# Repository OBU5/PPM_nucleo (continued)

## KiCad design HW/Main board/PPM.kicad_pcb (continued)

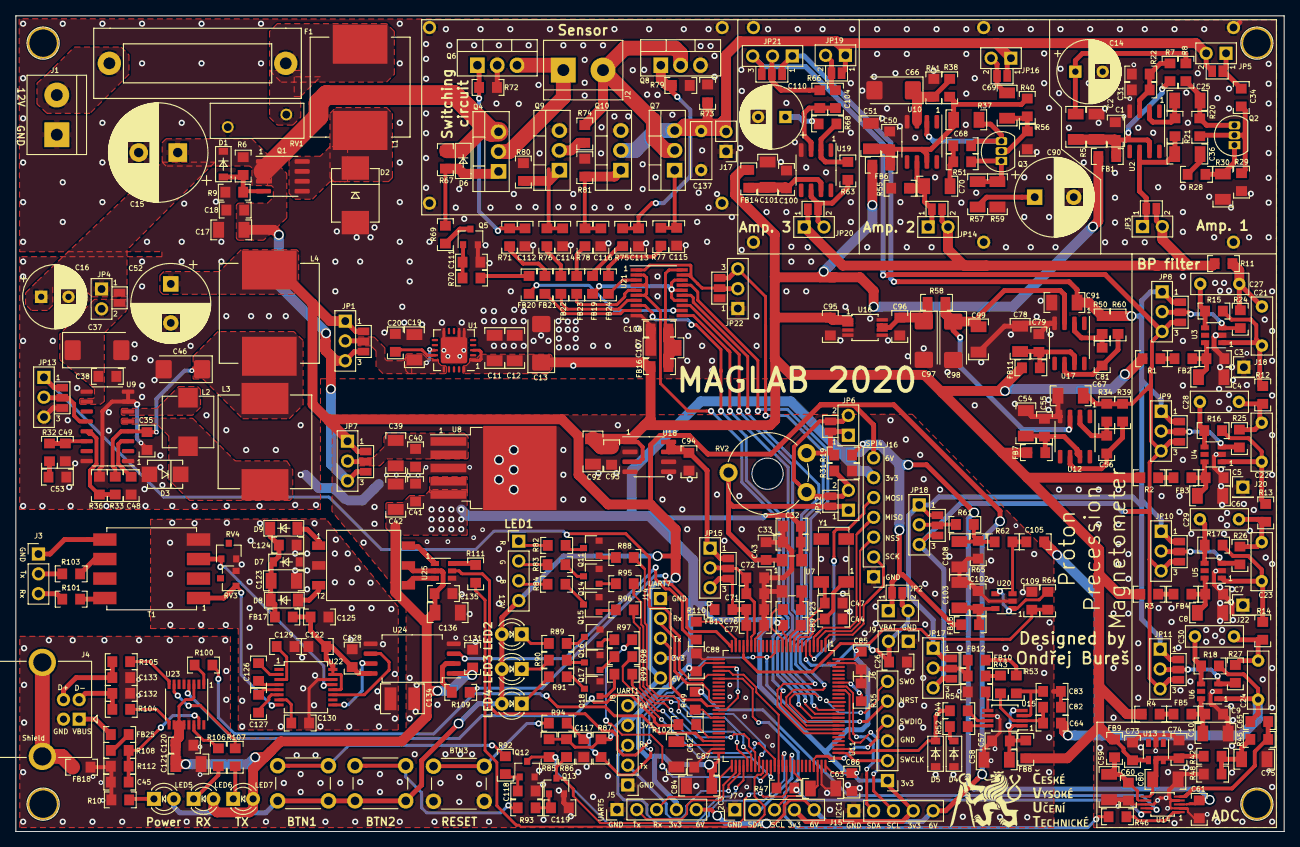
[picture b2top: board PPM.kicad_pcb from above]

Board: 2 copper layers, 162.5 x 104.5 mm, 400 parts (0 on the bottom side), 253 nets.

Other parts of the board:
C70: 22u; C1206
C81: 1u; C0805
C91: 10u; C1206
C111: 10n; C0805
C112, C113, C114, C115, C116: 100n; C0805
C137: C_res; C_Rect_L7.2mm_W2.5mm_P5.00mm_FKS2_FKP2_MKS2_MKP2
D6: 15V; D_SOD-123
J2: PPM_sensor; TerminalBlock_2pin_Pitch5.08mm
J17: C ext; PinHeader_1x02_P2.54mm_Vertical
Q4: IRF9640; TO-220-3_Vertical
Q5: BC847; SOT-23
Q6, Q7, Q9, Q10: IRF740; TO-220-3_Vertical
Q8: IRF640; TO-220-3_Vertical
R50, R67: 2k2; R0805
R55: 47k; R0805
R60: 47; R0805
R69: 1k; R0805
R70: 4k7; R0805
R71, R75, R76, R77, R78: 470; R0805
R72, R73, R79, R80, R81: 100k; R0805
R74: 10k; R0805

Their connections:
+12V: D6.1, Q4.3, R67.1; also elsewhere on the board
GNDA: C91.2, C111.2, C112.2, C113.2, C114.2, C115.2, C116.2, C137.2, J17.1, Q5.2, Q6.2, Q8.3, Q9.3, Q10.3, R55.2, R72.2, R73.2, R79.2, R80.2, R81.2; also elsewhere on the board
unnamed: C111.1, Q5.1, R70.2
unnamed: C112.1, Q6.1, R71.2, R72.1
unnamed: C113.1, Q8.1, R75.2, R79.1
unnamed: C114.1, Q9.1, R76.2, R80.1
unnamed: C115.1, Q7.1, R77.2
unnamed: C116.1, Q10.1, R78.2, R81.1
unnamed: D6.2, Q4.1, R67.2, R69.1
unnamed: J2.1, Q4.2, Q6.3
unnamed: J2.2, Q7.2, Q8.2, R74.1
unnamed: Q5.3, R69.2
unnamed: Q9.2, R74.2
S1_FET: R75.1; also elsewhere on the board
S2_FET: R77.1; also elsewhere on the board
S3_FET: R78.1; also elsewhere on the board
S4_FET: R70.1; also elsewhere on the board
S5_FET: R71.1; also elsewhere on the board
S6_FET: R76.1; also elsewhere on the board
Sig: C137.1, J17.2, Q7.3, Q10.2, R73.1; also elsewhere on the board

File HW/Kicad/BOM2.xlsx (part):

Ref | Value | Part | Footprint | Description | Code | count | which shopping cart | Column3 | Column6 | Column7 | Column8 | Column9 | Column10 | Column11 | Column12 | Column13 | Column14 | Column15 | Column16 | Column17 | Column18 | Column19 | Column20 | Column21 | Column22 | Column23 | Column24 | Column25 | Column26 | Column27 | Column28 | Column29 | Column30 | Column31 | Column32 | Column33 | Column34 | Column35 | Column36 | Column37 | Column38 | Column39 | Column40 | Column41 | Column42 | Column43 | Column44 | Column45 | Column46 | Column47 | Column48 | Column49 | Column50 | Column51 | Column52 | Column53 | Column54 | Column55 | Column56 | Column57 | Column58 | Column59 | Column60 | Column61 | Column62 | Column63 | Column64 | Column65 | Column66 | Column67 | Column68 | Column69 | Column70 | Column71 | Column72 | Column73 | Column74 | Column75 | Column76 | Column77 | Column78 | Column79 | Column80 | Column81 | Column82 | Column83 | Column84 | Column85 | Column86 | Column87 | Column88 | Column89 | Column90 | Column91 | Column92 | Column93 | Column94 | Column95 | Column96 | Column97 | Column98 | Column99 | Column100 | Column101 | Column102 | Column103 | Column104 | Column105 | Column106 | Column107 | Column108 | Column109 | Column110 | Column111 | Column112 | Column113 | Column114 | Column115 | Column116 | Column117 | Column118 | Column119 | Column120 | Column121 | Column122 | Column123 | Column124 | Column125 | Column126 | Column127 | Column128 | Column129 | Column130 | Column131 | Column132 | Column133 | Column134 | Column135 | Column136 | Column137 | Column138 | Column139 | Column140 | Column141 | Column142 | Column143 | Column144 | Column145 | Column146 | Column147 | Column148 | Column149 | Column150 | Column151 | Column152 | Column153 | Column154 | Column155 | Column156 | Column157 | Column158 | Column159 | Column160 | Column161 | Column162 | Column163 | Column164 | Column165 | Column166 | Column167 | Column168 | Column169 | Column170 | Column171 | Column172 | Column173 | Column174 | Column175 | Column176 | Column177 | Column178 | Column179 | Column180 | Column181 | Column182 | Column183 | Column184 | Column185 | Column186 | Column187 | Column188 | Column189 | Column190 | Column191 | Column192 | Column193 | Column194 | Column195 | Column196 | Column197 | Column198 | Column199 | Column200 | Column201 | Column202 | Column203 | Column204 | Column205 | Column206 | Column207 | Column208 | Column209 | Column210 | Column211 | Column212 | Column213 | Column214 | Column215 | Column216 | Column217 | Column218 | Column219 | Column220 | Column221 | Column222 | Column223 | Column224 | Column225 | Column226 | Column227 | Column228 | Column229 | Column230 | Column231 | Column232 | Column233 | Column234 | Column235 | Column236 | Column237 | Column238 | Column239 | Column240 | Column241 | Column242 | Column243 | Column244 | Column245 | Column246 | Column247 | Column248 | Column249 | Column250 | Column251 | Column252 | Column253 | Column254 | Column255 | Column256 | Column257 | Column258 | Column259 | Column260 | Column261 | Column262 | Column263 | Column264 | Column265 | Column266 | Column267 | Column268 | Column269 | Column270 | Column271 | Column272 | Column273 | Column274 | Column275 | Column276 | Column277 | Column278 | Column279 | Column280 | Column281 | Column282 | Column283 | Column284 | Column285 | Column286 | Column287 | Column288 | Column289 | Column290 | Column291 | Column292 | Column293 | Column294 | Column295 | Column296 | Column297 | Column298 | Column299 | Column300 | Column301 | Column302 | Column303 | Column304 | Column305 | Column306 | Column307 | Column308 | Column309 | Column310 | Column311 | Column312 | Column313 | Column314 | Column315 | Column316 | Column317 | Column318 | Column319 | Column320 | Column321 | Column322 | Column323 | Column324 | Column325 | Column326 | Column327 | Column328 | Column329 | Column330 | Column331 | Column332 | Column333 | Column334 | Column335 | Column336 | Column337 | Column338 | Column339 | Column340 | Column341 | Column342 | Column343 | Column344 | Column345 | Column346 | Column347 | Column348 | Column349 | Column350 | Column351 | Column352 | Column353 | Column354 | Column355 | Column356 | Column357 | Column358 | Column359 | Column360 | Column361 | Column362 | Column363 | Column364 | Column365 | Column366 | Column367 | Column368 | Column369 | Column370 | Column371 | Column372 | Column373 | Column374 | Column375 | Column376 | Column377 | Column378 | Column379 | Column380 | Column381 | Column382 | Column383 | Column384 | Column385 | Column386 | Column387 | Column388 | Column389 | Column390 | Column391 | Column392 | Column393 | Column394 | Column395 | Column396 | Column397 | Column398 | Column399 | Column400 | Column401 | Column402 | Column403 | Column404 | Column405 | Column406 | Column407 | Column408 | Column409 | Column410 | Column411 | Column412 | Column413 | Column414 | Column415 | Column416 | Column417 | Column418 | Column419 | Column420 | Column421 | Column422 | Column423 | Column424 | Column425 | Column426 | Column427 | Column428 | Column429 | Column430 | Column431 | Column432 | Column433 | Column434 | Column435 | Column436 | Column437 | Column438 | Column439 | Column440 | Column441 | Column442 | Column443 | Column444 | Column445 | Column446 | Column447 | Column448 | Column449 | Column450 | Column451 | Column452 | Column453 | Column454 | Column455 | Column456 | Column457 | Column458 | Column459 | Column460 | Column461 | Column462 | Column463 | Column464 | Column465 | Column466 | Column467 | Column468 | Column469 | Column470 | Column471 | Column472 | Column473 | Column474 | Column475 | Column476 | Column477 | Column478 | Column479 | Column480 | Column481 | Column482 | Column483 | Column484 | Column485 | Column486 | Column487 | Column488 | Column489 | Column490 | Column491 | Column492 | Column493 | Column494 | Column495 | Column496 | Column497 | Column498 | Column499 | Column500 | Column501 | Column502 | Column503 | Column504 | Column505 | Column506 | Column507 | Column508 | Column509 | Column510 | Column511 | Column512 | Column513 | Column514 | Column515 | Column516 | Column517 | Column518 | Column519 | Column520 | Column521 | Column522 | Column523 | Column524 | Column525 | Column526 | Column527 | Column528 | Column529 | Column530 | Column531 | Column532 | Column533 | Column534 | Column535 | Column536 | Column537 | Column538 | Column539 | Column540 | Column541 | Column542 | Column543 | Column544 | Column545 | Column546 | Column547 | Column548 | Column549 | Column550 | Column551 | Column552 | Column553 | Column554 | Column555 | Column556 | Column557 | Column558 | Column559 | Column560 | Column561 | Column562 | Column563 | Column564 | Column565 | Column566 | Column567 | Column568 | Column569 | Column570 | Column571 | Column572 | Column573 | Column574 | Column575 | Column576 | Column577 | Column578 | Column579 | Column580 | Column581 | Column582 | Column583 | Column584 | Column585 | Column586 | Column587 | Column588 | Column589 | Column590 | Column591 | Column592 | Column593 | Column594 | Column595 | Column596 | Column597 | Column598 | Column599 | Column600 | Column601 | Column602 | Column603 | Column604 | Column605 | Column606 | Column607 | Column608 | Column609 | Column610 | Column611 | Column612 | Column613 | Column614 | Column615 | Column616 | Column617 | Column618 | Column619 | Column620 | Column621 | Column622 | Column623 | Column624 | Column625 | Column626 | Column627 | Column628 | Column629 | Column630 | Column631 | Column632 | Column633 | Column634 | Column635 | Column636 | Column637 | Column638 | Column639 | Column640 | Column641 | Column642 | Column643 | Column644 | Column645 | Column646 | Column647 | Column648 | Column649 | Column650 | Column651 | Column652 | Column653 | Column654 | Column655 | Column656 | Column657 | Column658 | Column659 | Column660 | Column661 | Column662 | Column663 | Column664 | Column665 | Column666 | Column667 | Column668 | Column669 | Column670 | Column671 | Column672 | 
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
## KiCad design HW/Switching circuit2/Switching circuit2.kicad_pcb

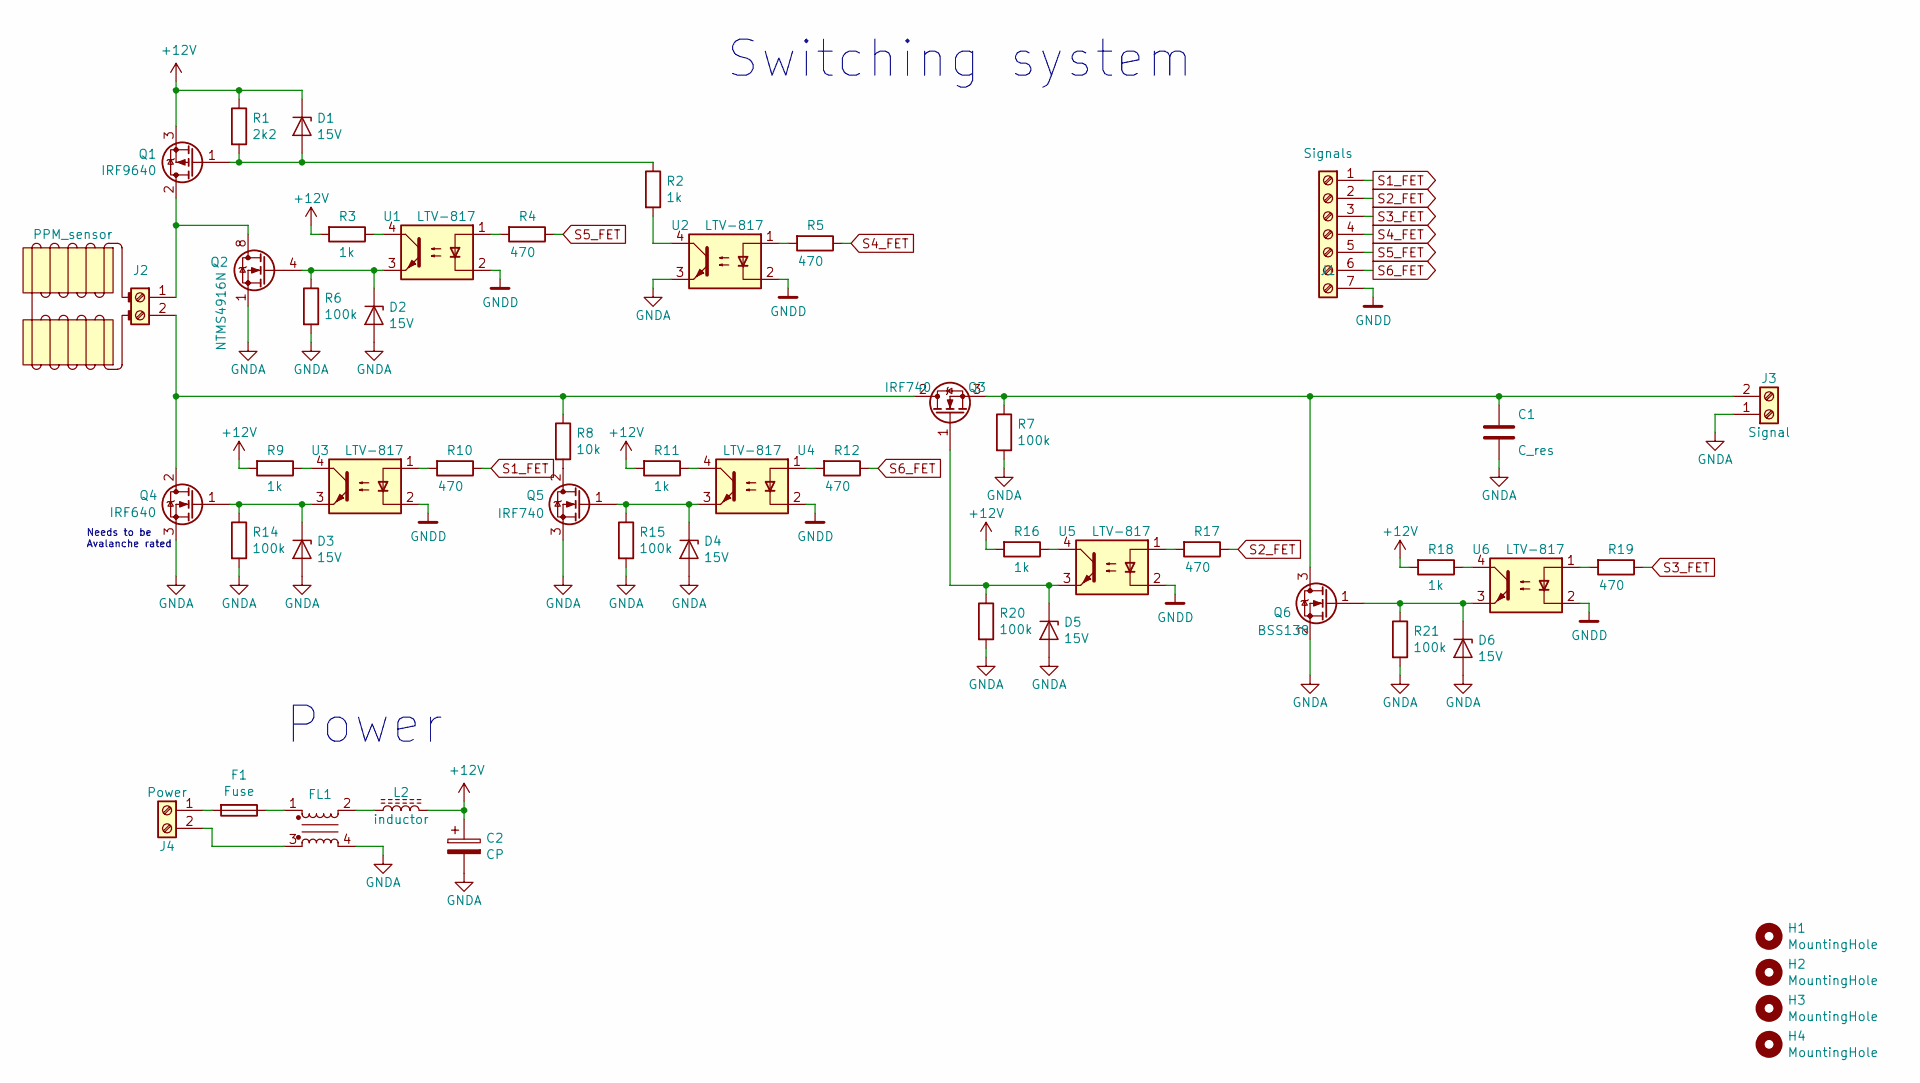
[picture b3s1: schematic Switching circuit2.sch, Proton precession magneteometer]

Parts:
C1: C_res; PinHeader_1x02_P2.54mm_Vertical
C2: CP; CP_Radial_D12.5mm_P5.00mm
D1, D2, D3, D4, D5, D6: 15V; D_SOD-123
F1: Fuse; Fuse_Holder-PTF15
FL1: EMI_Filter_CommonMode; Choke1
H1, H2, H3, H4: MountingHole; Screwh_hole-3.5mm
J1: Signals; PinHeader_1x07_P2.54mm_Vertical
J2: PPM_sensor; TerminalBlock_2pin_Pitch5.08mm
J3: Signal; PinHeader_1x02_P2.54mm_Vertical
J4: Power; TerminalBlock_2pin_Pitch5.08mm
L2: inductor; Inductor_SRR1208
Q1: IRF9640; TO-220-3_Vertical
Q2: NTMS4916N; SOIC-8_3.9x4.9mm_P1.27mm
Q3, Q5: IRF740; TO-220-3_Vertical
Q4: IRF640; TO-220-3_Vertical
Q6: BSS138; SOT-23
R1: 2k2; R1206
R2, R3, R9, R11, R16, R18: 1k; R1206
R4, R5, R10, R12, R17, R19: 470; R1206
R6, R7, R14, R15, R20, R21: 100k; R1206
R8: 10k; R1206
U1, U2, U3, U4, U5, U6: LTV-817; DIP-4_W8.89mm_SMDSocket_LongPads

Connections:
+12V: C2.1, D1.1 (K), L2.2, Q1.3 (S), R1.1, R3.2, R9.2, R11.2, R16.2, R18.2
GNDA: C1.2, C2.2, D2.2 (A), D3.2 (A), D4.2 (A), D5.2 (A), D6.2 (A), FL1.4, J3.1, Q2.1 (S), Q2.2 (S), Q2.3 (S), Q4.3 (S), Q5.3 (S), Q6.2 (S), R6.2, R7.2, R14.2, R15.2, R20.2, R21.2, U2.3
GNDD: J1.7, U1.2, U2.2, U3.2, U4.2, U5.2, U6.2
unnamed: C1.1, J3.2, Q3.3 (S), Q6.3 (D), R7.1
unnamed: D1.2 (A), Q1.1 (G), R1.2, R2.1
unnamed: D2.1 (K), Q2.4 (G), R6.1, U1.3
unnamed: D3.1 (K), Q4.1 (G), R14.1, U3.3
unnamed: D4.1 (K), Q5.1 (G), R15.1, U4.3
unnamed: D5.1 (K), Q3.1 (G), R20.1, U5.3
unnamed: D6.1 (K), Q6.1 (G), R21.1, U6.3
unnamed: F1.1, FL1.1
unnamed: F1.2, J4.1
unnamed: FL1.2, L2.1
unnamed: FL1.3, J4.2
unnamed: J2.1, Q1.2 (D), Q2.5 (D), Q2.6 (D), Q2.7 (D), Q2.8 (D)
unnamed: J2.2, Q3.2 (D), Q4.2 (D), R8.1
unnamed: Q5.2 (D), R8.2
unnamed: R2.2, U2.4
unnamed: R3.1, U1.4
unnamed: R4.2, U1.1
unnamed: R5.2, U2.1
unnamed: R9.1, U3.4
unnamed: R10.2, U3.1
unnamed: R11.1, U4.4
unnamed: R12.2, U4.1
unnamed: R16.1, U5.4
unnamed: R17.2, U5.1
unnamed: R18.1, U6.4
unnamed: R19.2, U6.1
S1_FET: J1.1, R10.1
S2_FET: J1.2, R17.1
S3_FET: J1.3, R19.1
S4_FET: J1.4, R5.1
S5_FET: J1.5, R4.1
S6_FET: J1.6, R12.1

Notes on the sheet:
Needs to be Avalanche rated
Switching system
Power

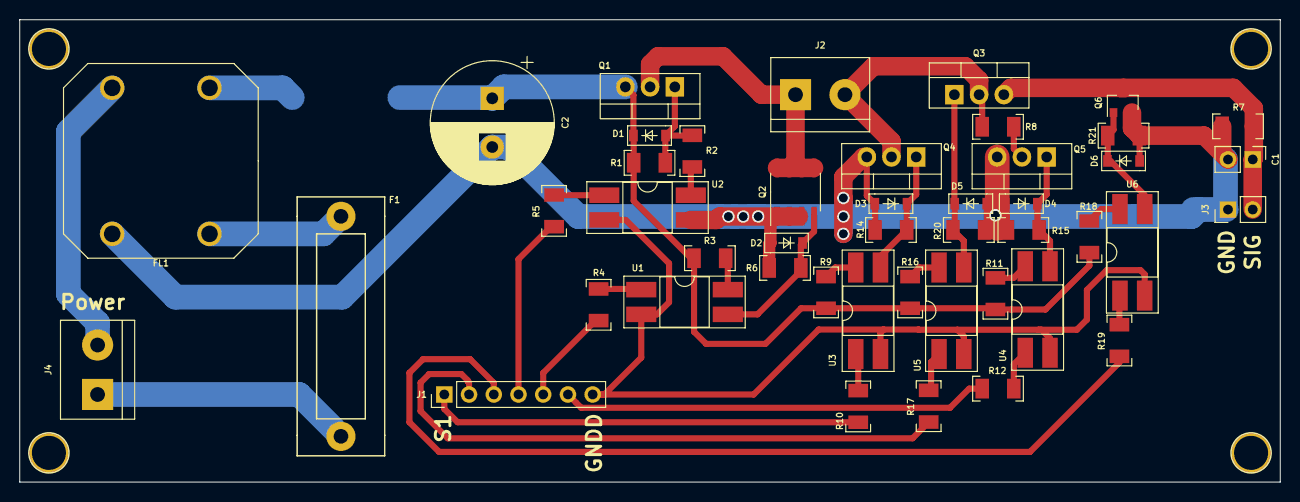
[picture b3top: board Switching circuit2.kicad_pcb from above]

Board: 2 copper layers, 129.5 x 47.5 mm, 51 parts (1 on the bottom side), 35 nets.

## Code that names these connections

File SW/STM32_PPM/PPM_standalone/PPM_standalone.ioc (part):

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Mcu.Name=STM32F767VITx
Mcu.Package=LQFP100
Mcu.UserName=STM32F767VITx
PA0/WKUP.GPIOParameters=GPIO_Label
PA0/WKUP.GPIO_Label=Amp_fil_sig-int_ADC
PA0/WKUP.Signal=ADCx_IN0
PA13.Mode=Trace_Asynchronous_SW
PA13.Signal=SYS_JTMS-SWDIO
PA14.Mode=Trace_Asynchronous_SW
PA14.Signal=SYS_JTCK-SWCLK
PA15.GPIOParameters=GPIO_Label
PA15.GPIO_Label=Comp
PA15.Signal=S_TIM2_CH1_ETR
PA2.GPIOParameters=GPIO_Label
PA2.GPIO_Label=UART2-TX_RS232
PA2.Mode=Asynchronous
PA2.Signal=USART2_TX
PA3.GPIOParameters=GPIO_Label
PA3.GPIO_Label=UART2-RX_RS232
PA3.Mode=Asynchronous
PA3.Signal=USART2_RX
PA4.GPIOParameters=GPIO_Label
PA4.GPIO_Label=SPI1-NSS_for_MCU
PA4.Mode=NSS_Signal_Hard_Input
PA4.Signal=SPI1_NSS
PA5.GPIOParameters=GPIO_Label
PA5.GPIO_Label=SPI1-CLK_ext_ADC
PA5.Mode=RX_Only_Simplex_Unidirect_Slave
PA5.Signal=SPI1_SCK
PA6.GPIOParameters=GPIO_Label
PA6.GPIO_Label=LT1777-SYNC
PA6.Signal=S_TIM3_CH1
PA7.GPIOParameters=GPIO_Label
PA7.GPIO_Label=SPI1-MOSI_ext_ADC
PA7.Mode=RX_Only_Simplex_Unidirect_Slave
PA7.Signal=SPI1_MOSI
PA8.Mode=I2C
PA8.Signal=I2C3_SCL
PB10.GPIOParameters=GPIO_Label
PB10.GPIO_Label=UART3-TX_FT230
PB10.Mode=Asynchronous
PB10.Signal=USART3_TX
PB11.GPIOParameters=GPIO_Label
PB11.GPIO_Label=UART3-RX_FT230
PB11.Mode=Asynchronous
PB11.Signal=USART3_RX
PB12.GPIOParameters=GPIO_Label
PB12.GPIO_Label=SYNC
PB12.Signal=GPXTI12
PB14.GPIOParameters=GPIO_Label
PB14.GPIO_Label=UART1-TX
PB14.Mode=Asynchronous
PB14.Signal=USART1_TX
PB15.GPIOParameters=GPIO_Label
PB15.GPIO_Label=UART1-RX
PB15.Mode=Asynchronous
PB15.Signal=USART1_RX
PB3.Mode=Trace_Asynchronous_SW
PB3.Signal=SYS_JTDO-SWO
PB6.Mode=I2C
PB6.Signal=I2C1_SCL
PB7.Mode=I2C
PB7.Signal=I2C1_SDA
PC14/OSC32_IN.Mode=LSE-External-Oscillator
PC14/OSC32_IN.Signal=RCC_OSC32_IN
PC15/OSC32_OUT.Mode=LSE-External-Oscillator
PC15/OSC32_OUT.Signal=RCC_OSC32_OUT
PC3.GPIOParameters=GPIO_Label
PC3.GPIO_Label=SN6505-EN
PC3.Signal=GPIO_Output
PC6.GPIOParameters=GPIO_Label
PC6.GPIO_Label=Gen_SPI1-CLK_for_ext_ADC
PC6.Signal=S_TIM8_CH1
PC7.GPIOParameters=GPIO_Label,GPIO_ModeDefaultEXTI
PC7.GPIO_Label=BTN1
PC7.GPIO_ModeDefaultEXTI=GPIO_MODE_IT_FALLING
PC7.Signal=GPXTI7
PC8.GPIOParameters=GPIO_Label,GPIO_ModeDefaultEXTI
PC8.GPIO_Label=BTN2
PC8.GPIO_ModeDefaultEXTI=GPIO_MODE_IT_FALLING
PC8.Signal=GPXTI8
PC9.Mode=I2C
PC9.Signal=I2C3_SDA
PD0.GPIOParameters=GPIO_Label
PD0.GPIO_Label=Switches_driver_enable
PD0.Signal=GPIO_Output
PD1.GPIOParameters=GPIO_Label
PD1.GPIO_Label=S1
PD1.Signal=GPIO_Output
PD10.GPIOParameters=GPIO_Label
PD10.GPIO_Label=LED1-B
PD10.Signal=GPIO_Output
PD11.GPIOParameters=GPIO_Label
PD11.GPIO_Label=SN6505-EN
PD11.Signal=GPIO_Output
PD12.GPIOParameters=GPIO_Label
PD12.GPIO_Label=SN6505-SYNC
PD12.Signal=S_TIM4_CH1
PD13.GPIOParameters=GPIO_Label
PD13.GPIO_Label=LED2
PD13.Signal=GPIO_Output
PD14.GPIOParameters=GPIO_Label
PD14.GPIO_Label=LED3
PD14.Signal=GPIO_Output
PD15.GPIOParameters=GPIO_Label
PD15.GPIO_Label=LED4
PD15.Signal=GPIO_Output
PD2.GPIOParameters=GPIO_Label
PD2.GPIO_Label=S2
PD2.Signal=GPIO_Output
PD3.GPIOParameters=GPIO_Label
PD3.GPIO_Label=S3
PD3.Signal=GPIO_Output
PD4.GPIOParameters=GPIO_Label
PD4.GPIO_Label=S4
PD4.Signal=GPIO_Output
PD5.GPIOParameters=GPIO_Label
PD5.GPIO_Label=S5
PD5.Signal=GPIO_Output
PD6.GPIOParameters=GPIO_Label
PD6.GPIO_Label=S6
PD6.Signal=GPIO_Output
PD8.GPIOParameters=GPIO_Label
PD8.GPIO_Label=LED1-R
PD8.Signal=GPIO_Output
PD9.GPIOParameters=GPIO_Label
PD9.GPIO_Label=LED1-G
PD9.Signal=GPIO_Output
PE11.GPIOParameters=GPIO_Label
PE11.GPIO_Label=Gen_SPI1-NSS_ext_ADC
PE11.Signal=S_TIM1_CH2
PE2.Mode=Full_Duplex_Master
PE2.Signal=SPI4_SCK
PE4.Mode=NSS_Signal_Hard_Output
PE4.Signal=SPI4_NSS
PE5.Mode=Full_Duplex_Master
PE5.Signal=SPI4_MISO
PE6.Mode=Full_Duplex_Master
PE6.Signal=SPI4_MOSI
PE7.Mode=Asynchronous
PE7.Signal=UART7_RX
PE8.Mode=Asynchronous
PE8.Signal=UART7_TX
PE9.GPIOParameters=GPIO_Label
PE9.GPIO_Label=Gen_SP1I-NSS_MCU
PE9.Signal=S_TIM1_CH1
PH0/OSC_IN.Mode=HSE-External-Oscillator
PH0/OSC_IN.Signal=RCC_OSC_IN
PH1/OSC_OUT.Mode=HSE-External-Oscillator
PH1/OSC_OUT.Signal=RCC_OSC_OUT
RCC.HSE_VALUE=10000000
RCC.SYSCLKFreq_VALUE=216000000
RCC.SYSCLKSource=RCC_SYSCLKSOURCE_PLLCLK
board=custom

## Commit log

2020-11-05 Working communication with MAX11100 over SPI
    SPI:
    receive only mode
    sending via interrupt generated with timer14
2020-11-05 SPI controlled via DMA from timer interrupt
    Configured in order to control the SPI via DMA... problem with clk -> 40 edges instead of 24 edges
2020-11-05 receiving ADC data from MAX11100 with frequency 44100 Hz and sending ADC value on UART
    It works, but it needs to be improved
    - data are sending on UART from callback
    - data are not stored to MCU over DMA
2020-11-15 Receive SPI signal (as slave) from external ADC over DMA
    In order to achieve saving only 2 bytes instead of 3 bytes (1. byte is always null) from external ADC, 2 timers were used
    TIM1 - Generates NSS for external ADC and NSS for MCU. NSS for MCU us low on 8th pulse of clk.
    TIM8 - generates 24 clk pulses and is triggerd on update event from TIM1.
2020-11-16 Modified SPI receive callback
    In order to be able to measure more than 65535 packets over DMA the code was modified. In the SPI receive callback was added part, where the function "HAL_SPI_Receive_DMA" is called again, but with e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
    Only problem is that the DMA is set all ower again, when all the data are received.
    Also, DMA low layer API was generated
2020-11-19 Added Input Capture timer to determine frequency from comparator
    In order to determine frequency from external comparator, TIM2 (32-bit) in input caputre mode was used.
2020-11-19 small modifications related to comparator
2020-11-23 Modified UART communication
    Data are now measured for time 2 seconds. After that 2 buffers are transfered via UART into computer
    - Modified order of bytes in existing uart communication. It was necessary beacuse befor in the code the data was obtained from SPI. Now the data are saved via DMA and the bytes order is "switched"
    ToDo: Frequency computation needs to be optimized
2020-12-06 Modified SPI pins
    Pins that will be used in PPM stand alone version were used in order to check, if everithing works with them.
2021-01-11 increased speed of UART from 115 200 bps to 2 000 000 bps
2021-01-13 added sechematic
2021-01-13 added PCB
2021-01-13 added gerber files
2021-01-13 added bill of materials
2021-01-13 removed unnecessary files
2021-01-13 Revert "Merge of PPM_standalone and PPM_nucleo versions"
    This reverts commit 0c80d330299ece87dfb9f1d4d4a5a3ec8442ced6.
2021-01-13 PPM_nucle moved in other directory
2021-01-13 added new file with PPM_Nucleo code
2021-01-13 Added PPM_Standalone version
2021-01-13 Added data acquisition scripts
    csvDataAnalysis.py - testing script that stores data into csv file
    serialCommunicationExample.py - testing script that enables communication over Serial port
    STM32_Communication.py - script that enables data acquisition from STM32
2021-01-13 added Matlab scripts that enables data analyzation
    data_part.mat - measured data by supervisor
    fit_damped_sinewave_fastOptimization.m and fit_damped_sinewave_fastOptimization.m - scripts that uses algorythm from Detlef Amberg that "fits data on damped sinewave"
    fit_damped_sinewave_Ver2.m - script that fits data on sinewave more efficiently. Algorythm was also designed by Detlef Amberg
2021-01-13 Revert "added new file with PPM_Nucleo code"
    This reverts commit b46cfa1d329759f94158fa1d5495cf02862698f2.
2021-01-13 Added PPM_Nucleo version
2021-01-14 changed Bill Of Material to correspond with filled cart on mouser
2021-01-14 added script "createPlot-example.py" that creates plot and implemented feature in the main script
2021-01-15 changed Bill Of Material to correspond with filled cart on mouser
    Added resistors around filter
2021-01-18 added the rest of components
2021-01-18 added Readme file
2021-01-21 Added possibility to send data from PC to board
2021-01-30 Added possibility to change measuring method
2021-01-31 added code that enables internal ADC controled by DMAand triggered by timer
2021-02-03 added polarization and measurement phase
    feature added, now it's necessary to merge it with the rest of code
2021-02-03 fixed errors after merge
2021-02-03 control of switching circuit was merged
    It runs before measuring phase
2021-02-03 Tasks merged, but continuous mode has some bugs
2021-02-03 changed print functions to make it easier for analysis
2021-02-08 implemented LED blinking on PPM standalone version
2021-02-08 implemented switching circuit control management
    Still needs to be tested on board
2021-02-10 code from nucleo implemented on standalone version
2021-02-11 bugfix - SPI communication set to 16bit on standalone version
2021-02-11 bugfix - changed timer to timer 6 on standalone version
2021-02-22 fixed problem with ADC over DMA
    In order to stop DMA conversion, it's necessary to set only register ADC1->CR2 &= ~ADC_CR2_DMA. if function HAL_ADC_Stop_DMA(&hadc1) would be called, it wouldn't be possible to Start DMA again.
2021-02-23 modified measuring of frequency via comparator
    - now the timer stores values over DMA into buffer
    - bugfix of timer robustness
2021-02-26 UART communication improvement
    In order to make the UART communication more stable and to have more options, UART communication was changed.
2021-02-27 bugfix - measurment method can be changed without any problems
2021-02-27 fixed problem with count of measurements
2021-03-01 fixed bugs and improved robustness+ add feature to change polarization time
2021-03-01 improvement of code readability
2021-03-01 Added comments to make the code more clear, added possibility to stop measuring through UART
2021-03-01 remove of unnecessary files from main folder
2021-03-02 improved stability with change of priorities, increased robustness of code and implemented desktop application
2021-03-02 added possibility to plot signal in desktop app
2021-03-03 Added feature on STM32 - measure every 20 seconds to keep constant period.
    the 20 seconds wait period runs in timer 5 (the same as timer used for delays)
2021-03-03 fixed bugs in schema
2021-03-04 changed TIM5 period to 50 us
2021-03-05 polarization time and measuring period changed in order to achieve faster results
2021-03-08 Modified getDataFromText.py script in order to see more details of signal
2021-03-12 Small modifications in python data acquisition script and polarization sequence in PPM_standalone was improved
    added state in polarization sequence
2021-03-14 added script to plot measured data from oscilloscope and fixed bug with SPI
    bugfix:
    boosted priority of DMA2 for SPI communication in order to fix problems with busy wait after RX. It seems that when he priority was low, than sometimes the settings for DMA wasn't fast enough and tha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
2021-03-15 added possibility to start MCU with measuring instead of polarization
2021-03-22 change of polarization sequence - it still needs work
2021-04-15 The device was constructed and finally bring to live
    There were some mistakes that are now fixed in schema, but still wrong on PCB. Keep it in mind...
2021-04-15 Changed Measurement sequence
    Still in progress
2021-04-20 improved data analysis in python in order to determine frequency using hilbert transform
    Also small modifications in firmware were implemented
    - fixed time between measurements
    - default measurement method is comparator with extADC
2021-05-04 firmware code was split from main to dedicated files to make the code more readable
2021-05-04 modification of python code hierarchy
2021-05-04 created python script that enables communication with STM32 standalone board
2021-05-04 fixed bug related to uart parse text on STM32. Also finished script in python that analyze and save measured data
2021-05-07 fixed bug related to data analysis in python
